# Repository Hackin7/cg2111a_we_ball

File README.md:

# cg2111a_we_ball

our robot will move as smoothly as a ball. Code here is modified from the template code with the various additions. More information about those additions can be found in our reports

# `main` branch

## PC - Client Code

Code found in `client_pc/tls-client-lib`. Compile using `compile.sh` and run `tls-alex-client <IP> <PORT>`.

# `main-rpi` branch

Repository should be put in `/home/pi/Documents/cg2111a_we_ball/`

## Arduino - Firmware Code

Code can be found in `/arduino/Alex`

For the `.ino` files, the compiler first loads the principal file (the one with the same name as the folder)
and then loads the others in alphabetical order. Concept behind multiple files can be found here: 
https://forum.arduino.cc/t/correct-way-to-include-multiple-files/507705/3 

Order of imports would be as such (think of it as combining into 1 big `.ino` file in this order)

```
Alex.ino
0_motors.ino
...
6_robotlib.ino
```

To get it to compile make sure to import `serialize.zip` as an arduino library first.

The compile and upload script for the firmware is in `arduino/upload.sh`

## RPi - Server Code

Can run  `server_rpi/start.sh`

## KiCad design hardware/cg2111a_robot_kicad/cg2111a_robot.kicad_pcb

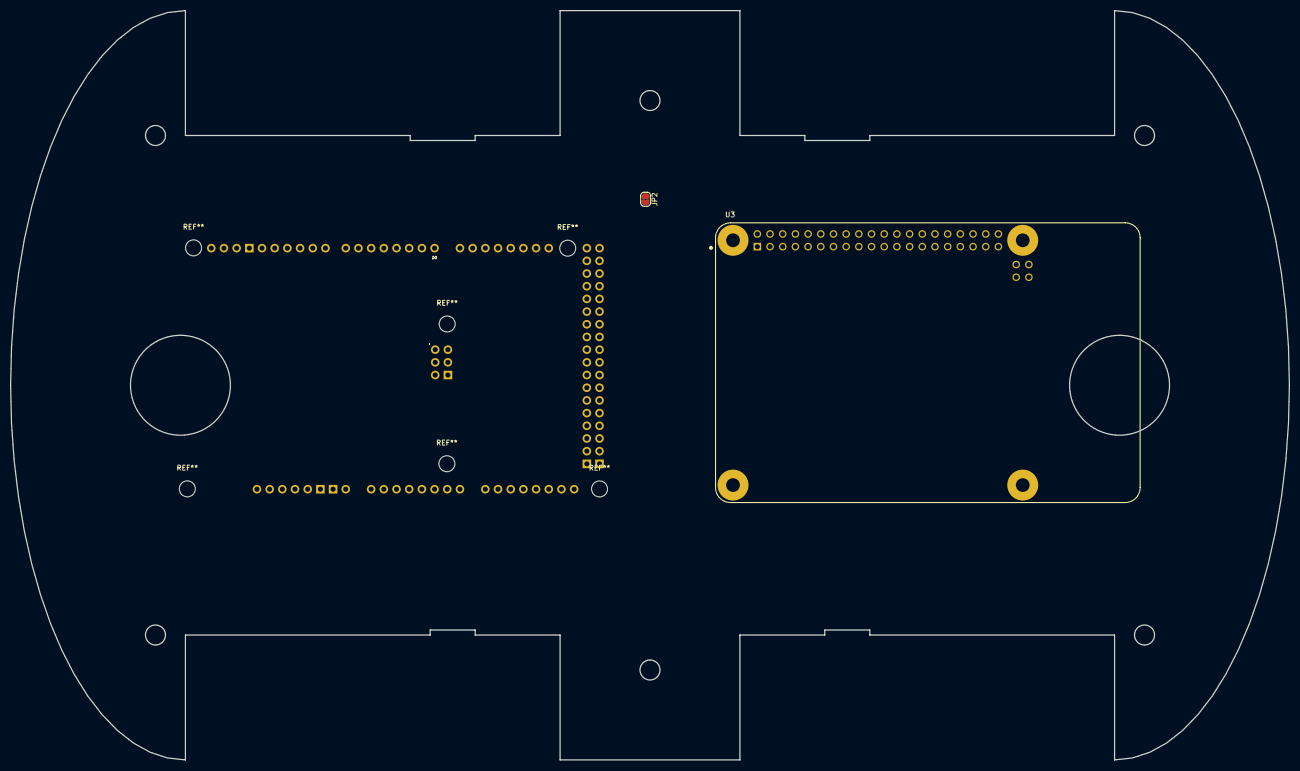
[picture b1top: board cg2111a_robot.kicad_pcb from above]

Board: 2 copper layers, 256.0 x 150.0 mm, 3 parts (0 on the bottom side), 4 nets, no tracks yet.

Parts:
JP2: SolderJumper_2_Bridged; SolderJumper-2_P1.3mm_Bridged2Bar_RoundedPad1.0x1.5mm
U3: RASPBERRY_PI_4B_4GB; MODULE_RASPBERRY_PI_4B_4GB
XA1: Arduino_Mega2560_Shield

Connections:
GND: U3.6 (GND), U3.9 (GND), U3.14 (GND), U3.20 (GND), U3.25 (GND), U3.30 (GND), U3.34 (GND), U3.39 (GND)
unnamed: U3.2 (5V), U3.4 (5V)
unnamed: U3.S1 (SHIELD), U3.S2 (SHIELD), U3.S3 (SHIELD), U3.S4 (SHIELD)
VCC: JP2.1 (A), U3.1 (3V3), U3.17 (3V3)

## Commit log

2024-03-22 feat: upload past lab code
2024-03-22 feat: rough breaking up of files
2024-03-25 rough import structure
2024-03-25 feat: split up 1
2024-03-25 feat: organisation
2024-03-25 chore: separate out arduino code
2024-03-25 add ros wasd code
2024-04-01 amended for consistency
2024-04-01 code structure improvements
2024-04-01 feat: compile scripts
2024-04-01 client side compile
2024-04-02 feat: server code test
2024-04-02 chore: remove binary files
2024-04-02 chore: ignore binary files
2024-04-02 chore: rename w9s2 folder to local_run
2024-04-02 fix: tls not reading issue
2024-04-02 keyboard basic control
2024-04-03 Created
2024-04-03 Update nibba
2024-04-03 Rename nibba to 7_colour_sensor.ino
2024-04-03 feat: motor debug stuff
2024-04-07 WIP code for interrupt-based USART
2024-04-10 additional baremetal conversion code
2024-04-13 backup 1
2024-04-13 basic upload system
2024-04-13 feat: ultrasonic but no dist
2024-04-13 feat: timing for motors
2024-04-13 rpi startup script tmux
2024-04-14 feat: tls working
2024-04-14 hardware + client changes
2024-04-14 feat: receive error message from client
2024-04-14 UI improvements
2024-04-14 reset & clear buffer on tls client
2024-04-14 feat: tls clear buffer
2024-04-14 improve UI
2024-04-14 motor basic odom using timers
2024-04-14 added delay to avoid spamming
2024-04-14 fix: ultrasonic semi bare-metal, encoders semi working (badly)
2024-04-14 feat: basic timers
2024-04-14 feat: basic timers - but auto start and stop
2024-04-14 feat: timers precision
2024-04-14 feat: baremetal serial receive
2024-04-15 move timer
2024-04-15 feat: ultrasonic packet
2024-04-15 feat: mock run 1
2024-04-17 feat: working backup
2024-04-22 final run adjustment
2024-04-22 final edits for final run
2024-04-26 colour enum
2024-04-26 bare metal serial tests
2024-04-28 updates and stuff
2024-07-19 chore: cleanup
2024-07-19 feat: added reports
2024-07-19 Create 3DModels folder
2024-07-19 Add files via upload
    Just some 3d models of the chassis for ALEX
